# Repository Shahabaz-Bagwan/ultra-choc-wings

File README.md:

# Ultra Choc Wings

A 36-key split keyboard for Kailh PG1316S switches, based on the
[Triboard](https://github.com/tarneaux/triboard).

* **36 keys**: 3×5 plus 3 thumb keys per half.
* **Chocofi layout**: 18 × 17 mm key spacing, the same column stagger and the
  same thumb cluster (0°, 15°, 30° fan) as the
  [chocofi](https://github.com/pashutk/chocofi), so keymaps, keycaps and muscle
  memory carry over. The stagger is Fifi's, which Chocofi kept in mm.
* **One reversible PCB** for both halves. The right half is the same board
  flipped over.
* **Per-key LEDs** (single colour, PWM dimmed, off by default).
* **CR2032 coin cell** per half, with a power switch.
* **ZMK with a dongle**: a third XIAO nRF52840 on USB is the central, both
  halves are low-power peripherals.
* **Seeed XIAO nRF52840** on each half.
* **JLCPCB ready**: gerbers, BOM and placement files for both halves; all SMD
  parts are assembled by JLCPCB on one side per half.
* **Two cases**: a thin folding case after Aronia's (opens flat as a uniboard,
  folds shut), and split trays that a tool-free slide-on clip joins into a rigid uniboard,
  or that work apart.

| Folder | What's in it |
| --- | --- |
| `config.yaml`, `footprints/` | Ergogen source of the PCB |
| `pcb/` | Routed KiCad board and DRC report |
| `jlcpcb/` | Gerbers, BOM and CPL files, [ordering guide](jlcpcb/README.md) |
| `firmware/` | ZMK config: dongle, left, right, keymap |
| `case/` | Folding and split cases, [notes](case/README.md) |
| `docs/power.md` | [Coin cell vs. LEDs](docs/power.md), the power budget |
| `archive/v1-lipo/` | The earlier hand-routed LiPo version |

## Coin cell and LEDs

A CR2032 cannot run 18 LEDs for long. The LEDs share one MOSFET, so when they
are off they draw nothing; the firmware keeps them off at boot, starts them at
10 % when you toggle them on (LOWER + RAISE, then `BL_TOG`), and turns them off
whenever the half goes idle. See [docs/power.md](docs/power.md) for the numbers
and the option of running from a LiPo instead.

## Firmware

`firmware/` is a ZMK user config (ZMK v0.3). GitHub Actions builds it on every
push (`.github/workflows/zmk.yml`); download the `firmware` artifact and flash:

* `ultra_choc_wings_dongle` onto the XIAO that stays plugged into the computer,
* `ultra_choc_wings_left` and `ultra_choc_wings_right` onto the halves,
* `settings_reset` first if the boards were paired to something before.

The keymap is `firmware/ultra_choc_wings.keymap` (QWERTY with LOWER, RAISE and
ADJUST layers).

## Building the PCB

```sh
npm install
KICAD_PYTHON=python3 FREEROUTING_JAR=path/to/freerouting.jar scripts/build_pcb.sh
```

This runs Ergogen, autoroutes with [Freerouting](https://github.com/freerouting/freerouting),
joins the few connections Freerouting misreads around the flippable XIAO
pads (`scripts/finish_routes.py`), adds ground pours on both layers, writes a DRC report, exports gerbers, the
JLCPCB BOM/CPL files, the schematic and the cases. It needs KiCad 7 or newer (with its Python
module), Java, and `xvfb-run` on a headless machine. The committed board was
autorouted; review it in KiCad before ordering and hand-tidy any routes you
don't like.

`pcb/drc.rpt` has no unconnected items. The remaining entries are known: the
flippable XIAO footprint's solder jumpers sit closer than the default clearance
and hole clearance by design, solder mask bridges between those jumpers,
library-footprint notes (KiCad compares the generated footprints with the
`ucw` library), and silkscreen overlaps.

## Schematic and libraries

The board comes from Ergogen, so `scripts/make_schematic.py` writes the
KiCad side from the routed board (it runs as part of `build_pcb.sh`):

* `pcb/ultra-choc-wings.kicad_sch`: every part of one half with its nets,
  as net labels, grouped into the key matrix, MCU, power and LED driver.
* `pcb/ucw.kicad_sym`: one symbol per part type.
* `pcb/ucw.pretty/`: one footprint per part type, taken from the board.
* `pcb/fp-lib-table`, `pcb/sym-lib-table`: point the project at both.

Every part also has a simple STEP 3D model (`pcb/ucw.3dshapes/`, boxes and
cylinders from the datasheet outlines, not exact CAD), so KiCad's 3D viewer
and its STEP export (File > Export > STEP) show the populated board; `docs/board-3d-parts.png` is the same without
keycaps. The switches use the real Kailh STEP model (`PG1316S.step`, copied from
`library/leptiosis.pretty`); the mounting holes and the test pad have no 3D
model. The preview images still draw the switch as a simple box.
`scripts/make_3d_models.py` writes them and links them into the board
and the `ucw` footprints, also for switches swapped to the `leptiosis` footprint. The models sit on the switch side, the front (F)
for the left half.

Every footprint on the board is linked to its `ucw` footprint and to its
schematic symbol, so cross-probing and "Update PCB from Schematic" match part
for part. Change the design in `config.yaml` and rerun the build rather than
editing the schematic; the build overwrites it.

## Assembly notes

* All SMD parts, the switches and the XIAO go on the **same side** of each
  PCB: the front for the left half, the back for the right half.
* Bridge the `[> ]` jumper pads under the XIAO on the side the XIAO sits on.
* Wire the **RAW** pad (next to the XIAO) to the BAT+ pad under the XIAO.

## Credits

- Inspiration: keyboards by [GEIGEIGEIST](https://github.com/GEIGEIGEIST), the [chocofi](https://github.com/pashutk/chocofi) and the [samoklava](https://github.com/wxsh/samoklava).
- Videos by Ben Vallack on YouTube.
- Kind people on the [ErgoMechKeyboards](https://lemmy.ml/c/ergomechkeyboards@lemmy.world) Lemmy community.
- FlatFootFox - [Let's Design A Keyboard With Ergogen v4](https://flatfootfox.com/ergogen-introduction/)

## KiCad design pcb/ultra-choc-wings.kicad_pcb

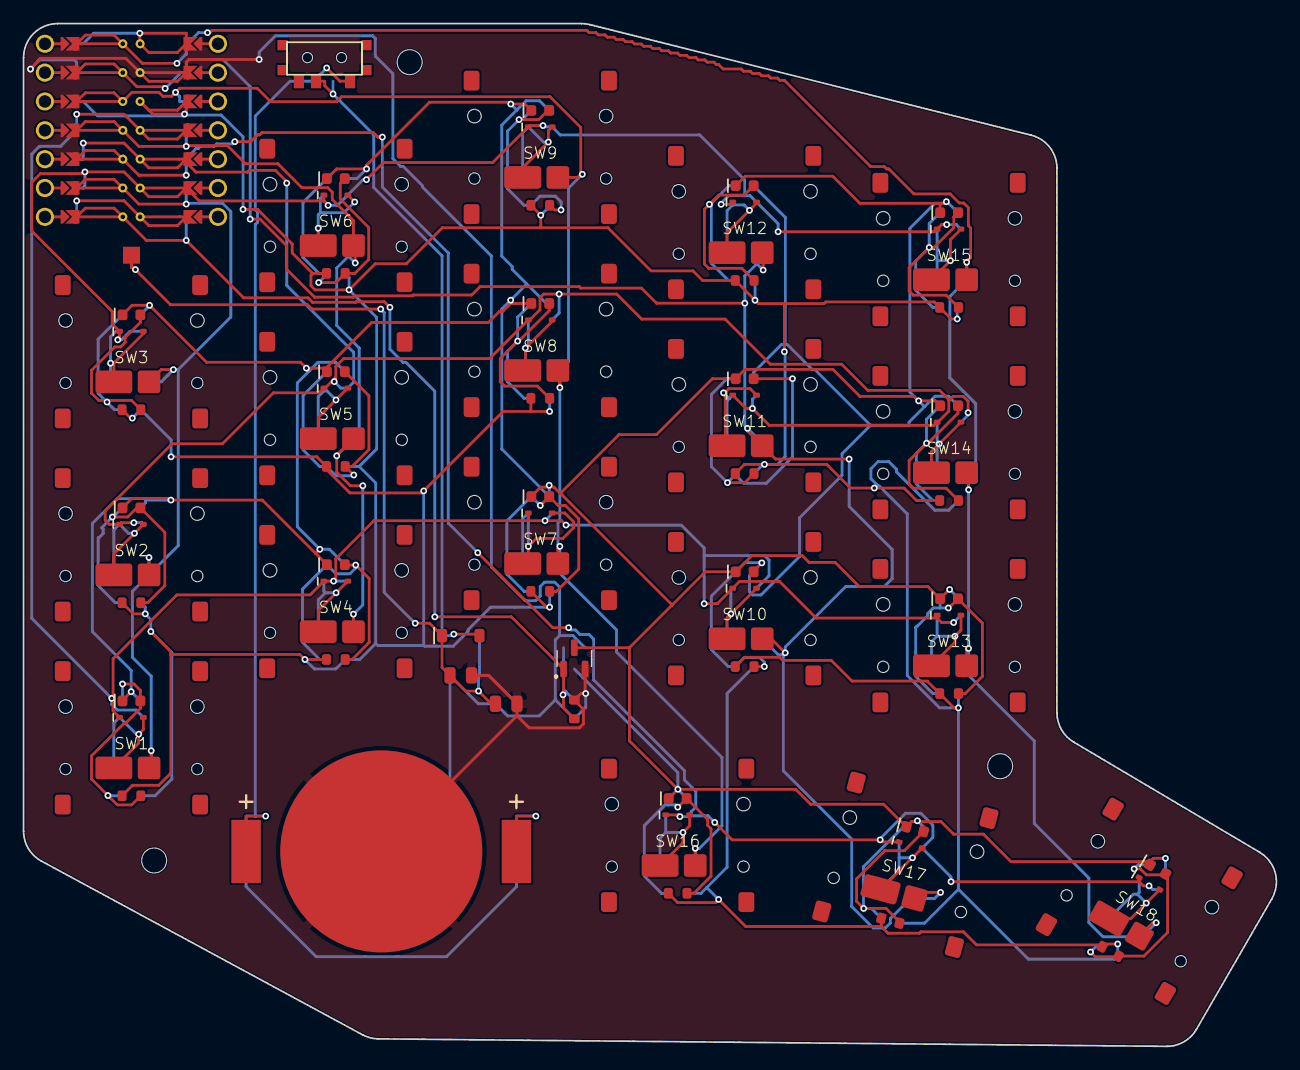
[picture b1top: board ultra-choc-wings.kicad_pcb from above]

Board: 2 copper layers, 110.3 x 90.1 mm, 84 parts (0 on the bottom side), 52 nets.

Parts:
BT1: CR2032; REV_CR2032_BC2003
C1, C2: 22uF; REV_0805
D1, D2, D3, D4, D5, D6, D7, D8, D9, D10, D11, D12, D13, D14, D15, D16, D17, D18: 1N4148WS; REV_SOD323
D19: B5819W; REV_SOD123
H1, H2, H3: M2; M2_NPTH
L1, L2, L3, L4, L5, L6, L7, L8, L9, L10, L11, L12, L13, L14, L15, L16, L17, L18: LED_red_0603; REV_LED0603
PAD1: SMDPad
Q1: AO3400A; REV_SOT-23
R1, R2, R3, R4, R5, R6, R7, R8, R9, R10, R11, R12, R13, R14, R15, R16, R17, R18: 1k; REV_0603
R19: 100k; REV_0603
SW1, SW2, SW3, SW4, SW5, SW6, SW7, SW8, SW9, SW10, SW11, SW12, SW13, SW14, SW15, SW16, SW17, SW18: CPG1316S01D02_reversible_mikefives
T1: REV_SPDT_C128955
xiao-ble1: ProMicro; xiao-ble

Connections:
BAT: BT1.1, T1.1
GND: BT1.2, C1.2, C2.2, Q1.2, R19.2, xiao-ble1.2
LA_home_thumb: L18.2, R18.2
LA_index_bottom: L10.2, R10.2
LA_index_home: L11.2, R11.2
LA_index_top: L12.2, R12.2
LA_inner_bottom: L13.2, R13.2
LA_inner_home: L14.2, R14.2
LA_inner_thumb: L16.2, R16.2
LA_inner_top: L15.2, R15.2
LA_middle_bottom: L7.2, R7.2
LA_middle_home: L8.2, R8.2
LA_middle_thumb: L17.2, R17.2
LA_middle_top: L9.2, R9.2
LA_pinky_bottom: L1.2, R1.2
LA_pinky_home: L2.2, R2.2
LA_pinky_top: L3.2, R3.2
LA_ring_bottom: L4.2, R4.2
LA_ring_home: L5.2, R5.2
LA_ring_top: L6.2, R6.2
LED_K: L1.1, L2.1, L3.1, L4.1, L5.1, L6.1, L7.1, L8.1, L9.1, L10.1, L11.1, L12.1, L13.1, L14.1, L15.1, L16.1, L17.1, L18.1, Q1.3
P0: SW13.2, SW14.2, SW15.2, SW18.2, xiao-ble1.24
P1: SW10.2, SW11.2, SW12.2, SW17.2, xiao-ble1.23
P2: SW7.2, SW8.2, SW9.2, SW16.2, xiao-ble1.22
P3: SW4.2, SW5.2, SW6.2, xiao-ble1.21
P4: D16.1, D17.1, D18.1, xiao-ble1.20
P5: SW1.2, SW2.2, SW3.2, xiao-ble1.19
P6: Q1.1, R19.1, xiao-ble1.18
P8: D3.1, D6.1, D9.1, D12.1, D15.1, xiao-ble1.6
P9: D2.1, D5.1, D8.1, D11.1, D14.1, xiao-ble1.5
P10: D1.1, D4.1, D7.1, D10.1, D13.1, xiao-ble1.4
RAW: C1.1, C2.1, D19.1, PAD1.1
SW_BAT: D19.2, T1.2
VCC3: R1.1, R2.1, R3.1, R4.1, R5.1, R6.1, R7.1, R8.1, R9.1, R10.1, R11.1, R12.1, R13.1, R14.1, R15.1, R16.1, R17.1, R18.1, xiao-ble1.3
home_thumb: D18.2, SW18.1
index_bottom: D10.2, SW10.1
index_home: D11.2, SW11.1
index_top: D12.2, SW12.1
inner_bottom: D13.2, SW13.1
inner_home: D14.2, SW14.1
inner_thumb: D16.2, SW16.1
inner_top: D15.2, SW15.1
middle_bottom: D7.2, SW7.1
middle_home: D8.2, SW8.1
middle_thumb: D17.2, SW17.1
middle_top: D9.2, SW9.1
pinky_bottom: D1.2, SW1.1
pinky_home: D2.2, SW2.1
pinky_top: D3.2, SW3.1
ring_bottom: D4.2, SW4.1
ring_home: D5.2, SW5.1
ring_top: D6.2, SW6.1

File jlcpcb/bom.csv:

Comment,Designator,Footprint,LCSC Part #
Resistor 100k 1% 0603,R19,0603,C25803
Switching diode 1N4148W,"D1,D2,D3,D4,D5,D6,D7,D8,D9,D10,D11,D12,D13,D14,D15,D16,D17,D18",SOD-123,C81598
Resistor 1k 1% 0603,"R1,R2,R3,R4,R5,R6,R7,R8,R9,R10,R11,R12,R13,R14,R15,R16,R17,R18",0603,C21190
Capacitor 22uF 25V X5R 0805,"C1,C2",0805,C45783
N-MOSFET AO3400A,Q1,SOT-23,C20917
Schottky diode 40V 1A B5819W,D19,SOD-123,C8598
LED red 0603,"L1,L2,L3,L4,L5,L6,L7,L8,L9,L10,L11,L12,L13,L14,L15,L16,L17,L18",0603,C2286
Slide switch SPDT (C128955 land pattern),T1,SMD,C128955

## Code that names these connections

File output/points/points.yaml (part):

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        autobind: 10
        skip: false
        asym: both
        colrow: pinky_bottom
        name: matrix_pinky_bottom
        column_net: P5
        row_net: P10
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        autobind: 10
        skip: false
        asym: both
        colrow: pinky_home
        name: matrix_pinky_home
        column_net: P5
        row_net: P9
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        autobind: 10
        skip: false
        asym: both
        colrow: pinky_top
        name: matrix_pinky_top
        column_net: P5
        row_net: P8
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
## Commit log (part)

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2025-09-09 feat(choc-ultra): add choc-ultra placing
2025-09-09 feat(pg1316s): add reversible switch layout
2025-09-09 fix(layout): add splay and library for footprint
2025-09-09 chore(pcb): add extra parts
2025-09-10 Revert "chore(pcb): add extra parts"
    This reverts commit bf00a23c4da58c788347c8aacf8456471ae03a72.
2025-09-10 feat(battery_connector): add footprint and use battery connector instead of solder pad
2025-09-10 feat(pcb): add pcb files generated by ergogen
2025-09-10 fix(routing): route pcb
2025-09-10 feat(3dmodel): add 3d model of swtich
2025-09-10 fix(battery): connect battery connector with slider switch
2025-09-10 feat(gerber): add gerber files
2025-09-10 add photo
2025-09-11 chore(silkscreen): add markings
2025-09-11 fix(splay): rotate middle thumb key by 5 degree and move 1 mm out
2025-09-12 feat(led): add led
